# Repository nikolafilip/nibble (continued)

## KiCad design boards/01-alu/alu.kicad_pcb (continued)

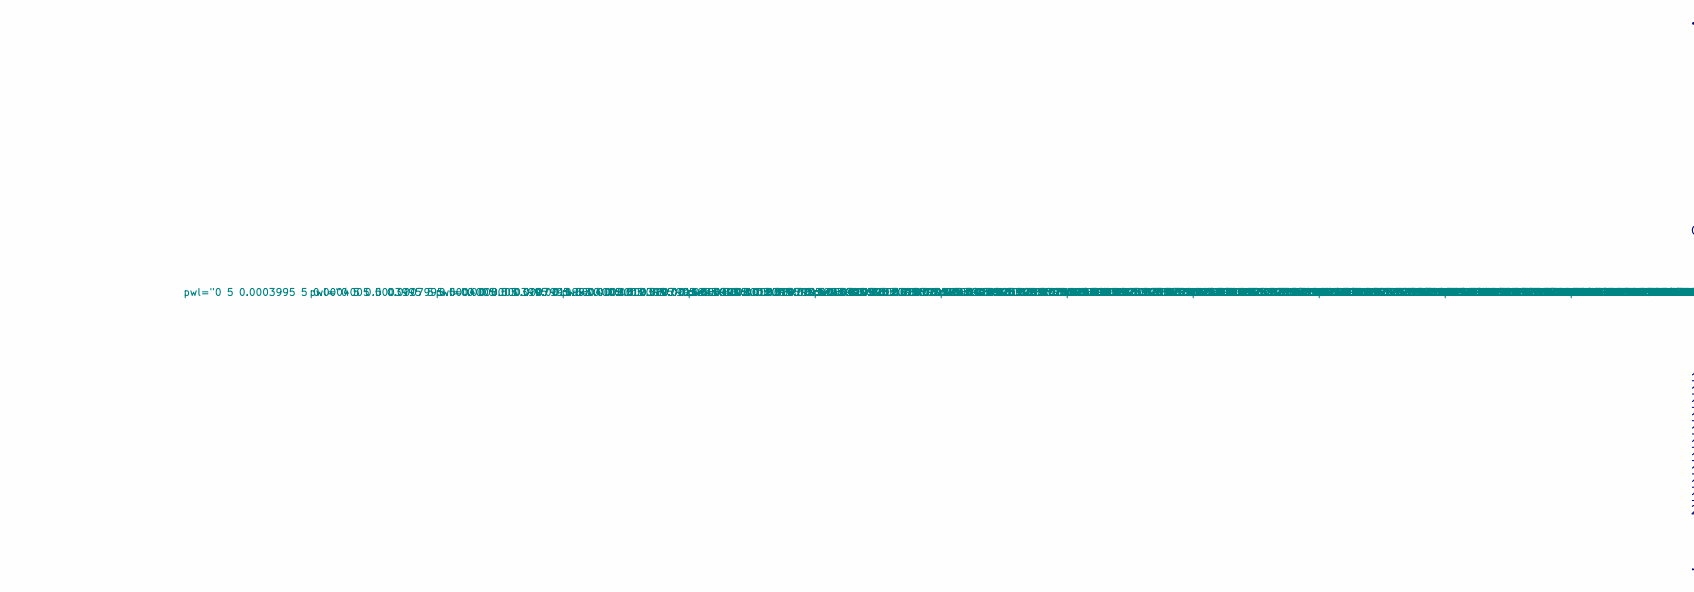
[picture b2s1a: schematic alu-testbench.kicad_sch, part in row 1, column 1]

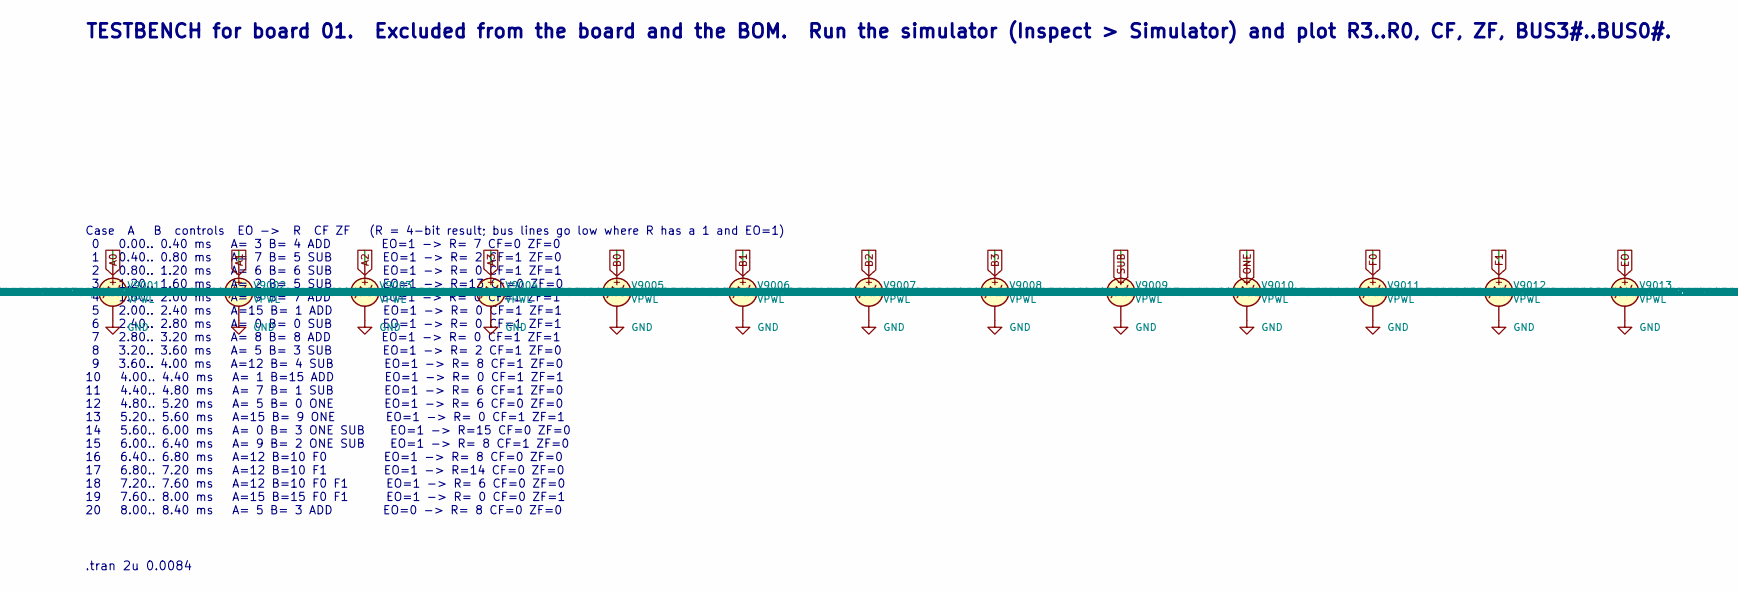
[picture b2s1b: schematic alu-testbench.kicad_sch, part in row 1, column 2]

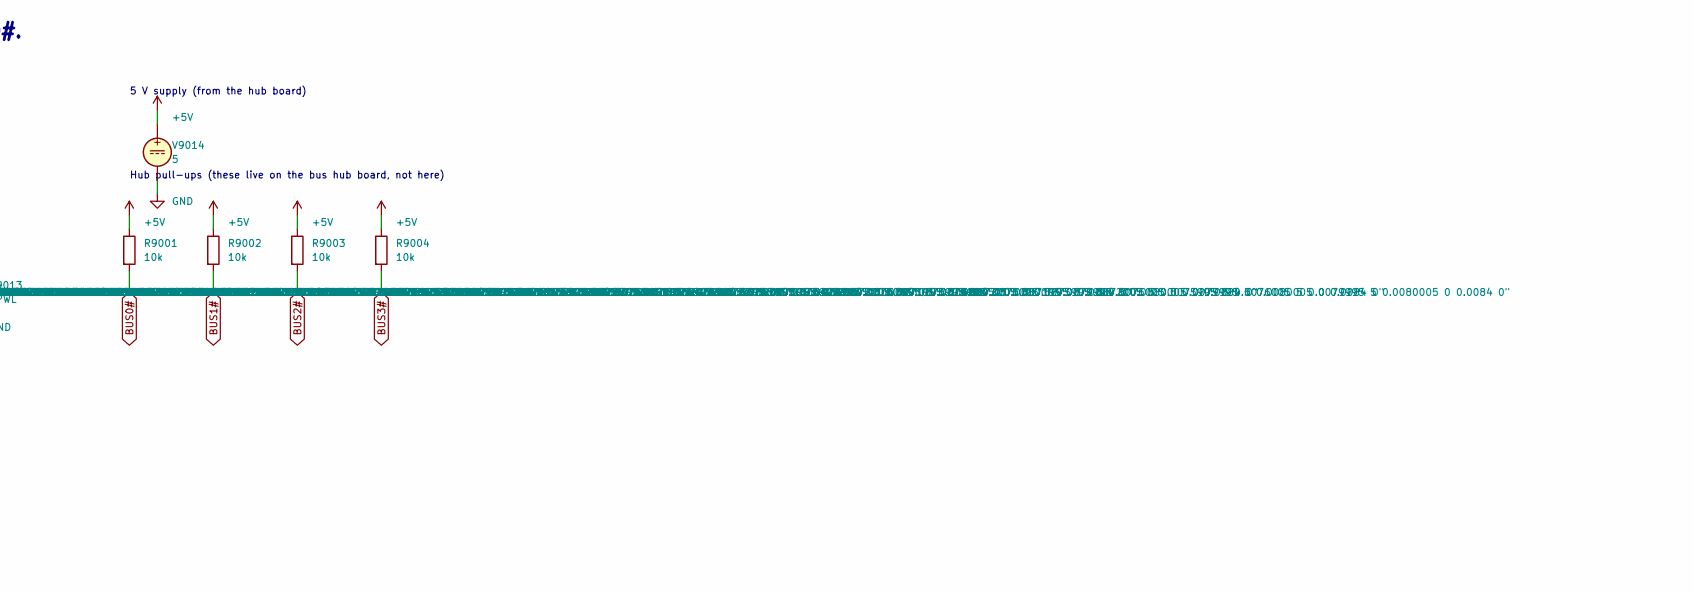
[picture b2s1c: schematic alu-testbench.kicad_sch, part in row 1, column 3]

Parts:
R9001, R9002, R9003, R9004: 10k
V9001, V9002, V9003, V9004, V9005, V9006, V9007, V9008, V9009, V9010, V9011, V9012, V9013: VPWL
V9014: 5

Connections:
unnamed: R9001.1, R9002.1, R9003.1, R9004.1, V9014.1
unnamed: V9001.2, V9002.2, V9003.2, V9004.2, V9005.2, V9006.2, V9007.2, V9008.2, V9009.2, V9010.2, V9011.2, V9012.2, V9013.2, V9014.2

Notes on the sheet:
TESTBENCH for board 01. Excluded from the board and the BOM. Run the simulator (Inspect > Simulator) and plot R3..R0, CF, ZF, BUS3#..BUS0#.
Case A B controls EO -> R CF ZF (R = 4-bit result; bus lines go low where R has a 1 and EO=1) 0 0.00.. 0.40 ms A= 3 B= 4 ADD EO=1 -> R= 7 CF=0 ZF=0 1 0.40.. 0.80 ms A= 7 B= 5 SUB EO=1 -> R= 2 CF=1 ZF=0 2 0.80.. 1.20 ms A= 6 B= 6 SUB EO=1 -> R= 0 CF=1 ZF=1 3 1.20.. 1.60 ms A= 2 B= 5 SUB EO=1 -> R=13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
.tran 2u 0.0084
5 V supply (from the hub board)
Hub pull-ups (these live on the bus hub board, not here)

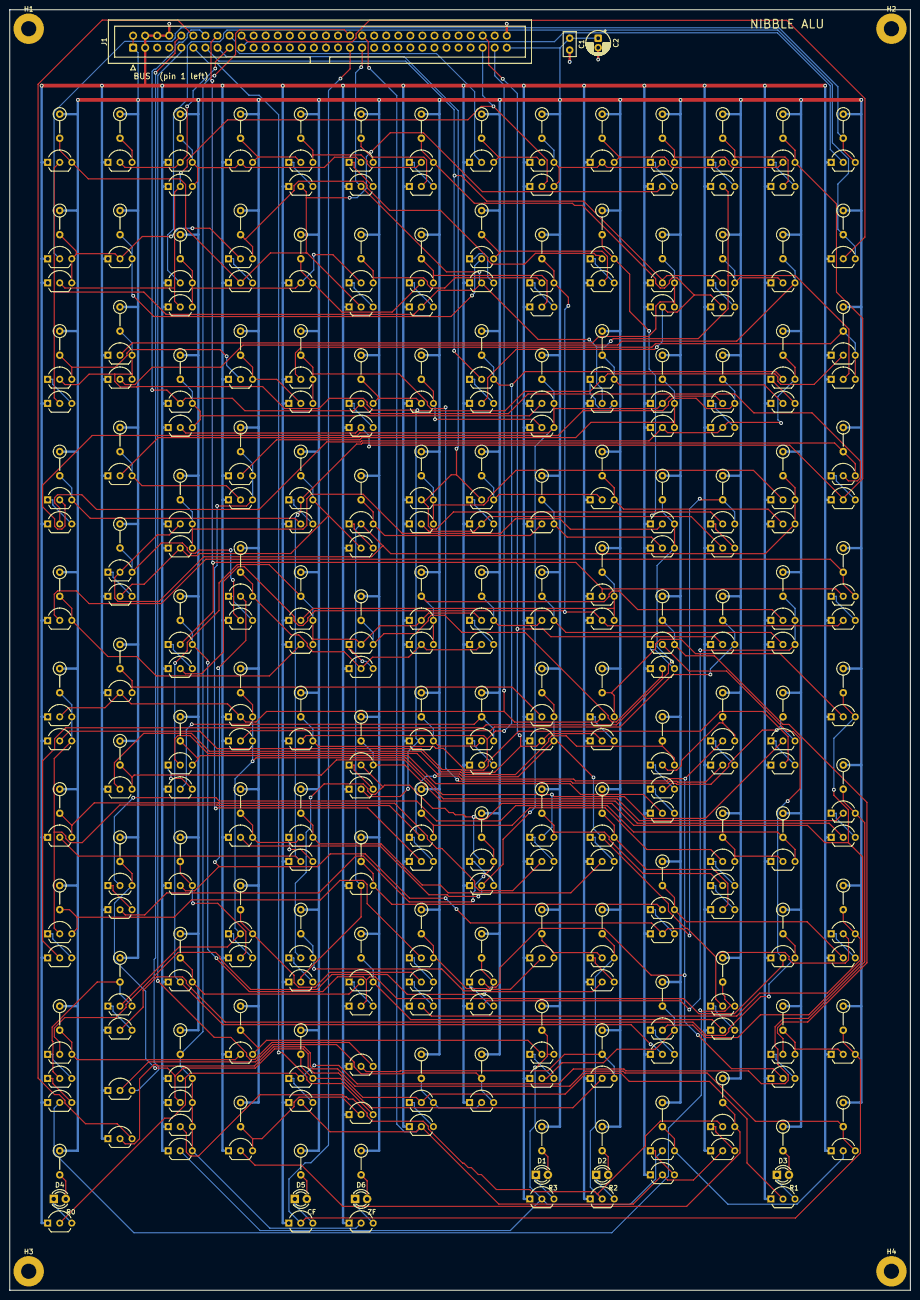
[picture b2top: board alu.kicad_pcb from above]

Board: 2 copper layers, 189.8 x 269.8 mm, 379 parts (0 on the bottom side), 228 nets.

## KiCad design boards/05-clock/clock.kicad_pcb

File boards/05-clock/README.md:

# Board 05: clock

The clock, the speed knob, the RUN/STEP switch, the halt gate and the
power-on reset. 14 transistors in cells plus the two of the Schmitt trigger,
one pot, one DIP switch, one jumper.

| | |
|---|---|
| Bus signals used | in: HLT. out: CLK, RST |

- **Oscillator**: a source-coupled Schmitt trigger (Q1 and Q2 share a 1k
  source resistor; Q2's 10k load and Q1's 47k load put the source at 0.45 V
  and 0.1 V) reads the RC node X and trips at Vth + 0.55 V going up, Vth +
  0.15 V going down. Both trip points move with the same transistor's
  threshold, so the hysteresis survives any threshold spread. Its output is
  Q2's drain, inverted by SA (4.7k pull-up), which charges X through 100k plus
  the 1M pot. 47 nF on X gives roughly 500 Hz down to 40 Hz; the SLOW jumper
  adds 2.2 uF for 10 Hz down to 0.8 Hz.
- **RUN**: the switch puts +5 V through a diode and 10k onto CLK, and the
  oscillator's transistor pulls CLK low for half of each cycle. **STEP**: the
  switch is open, the transistor is held off, and the panel's CLK button owns
  the line. The diode keeps the 10k from loading the button in STEP.
- **HLT** high holds CLK low.
- **Power-on reset**: 2.2 uF charging through 100k into a Schmitt trigger
  holds RST high for about a tenth of a second after power-up.

Three oscillators failed in simulation before this one (D036): two plain
inverters with an RC settle at a stable operating point; a MOSFET astable
falls into its both-on state; and reading the Schmitt trigger at the wrong
node let the outer loop settle half way. The mixed-threshold corner found
every one of them.

Generated by `sim/build_clock.py` from `sim/clock.py`; `sim/tb_clock.py`
measures period, duty, halt, step and the reset pulse at every corner.

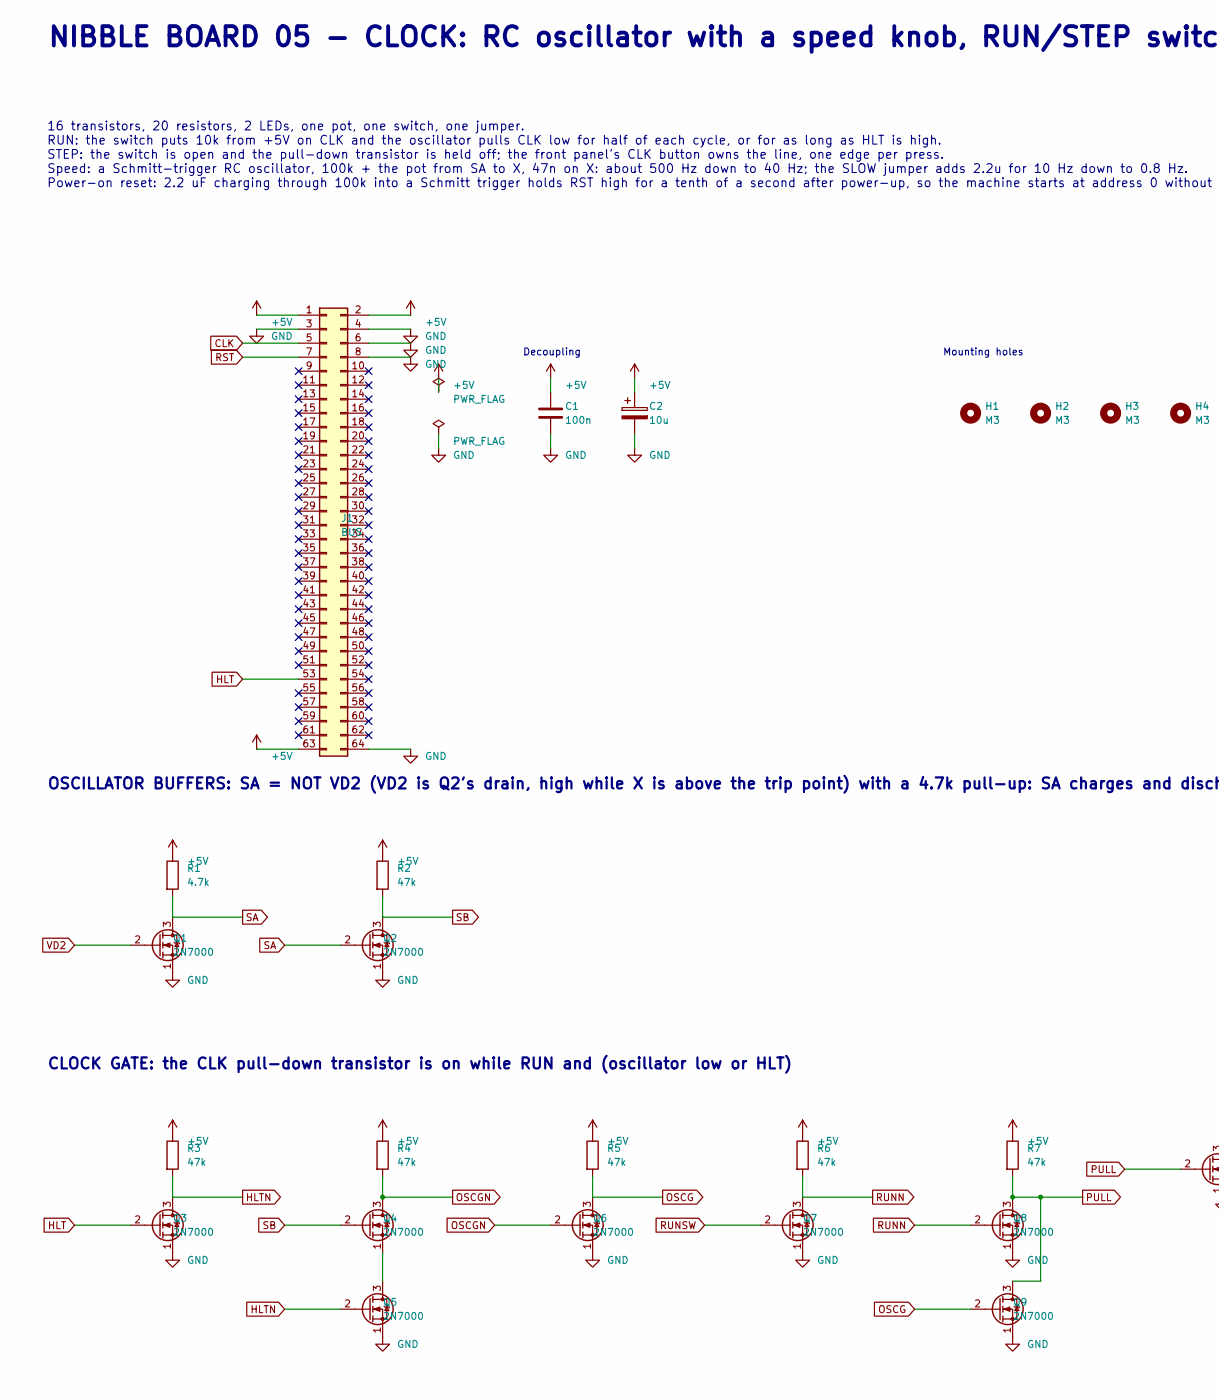
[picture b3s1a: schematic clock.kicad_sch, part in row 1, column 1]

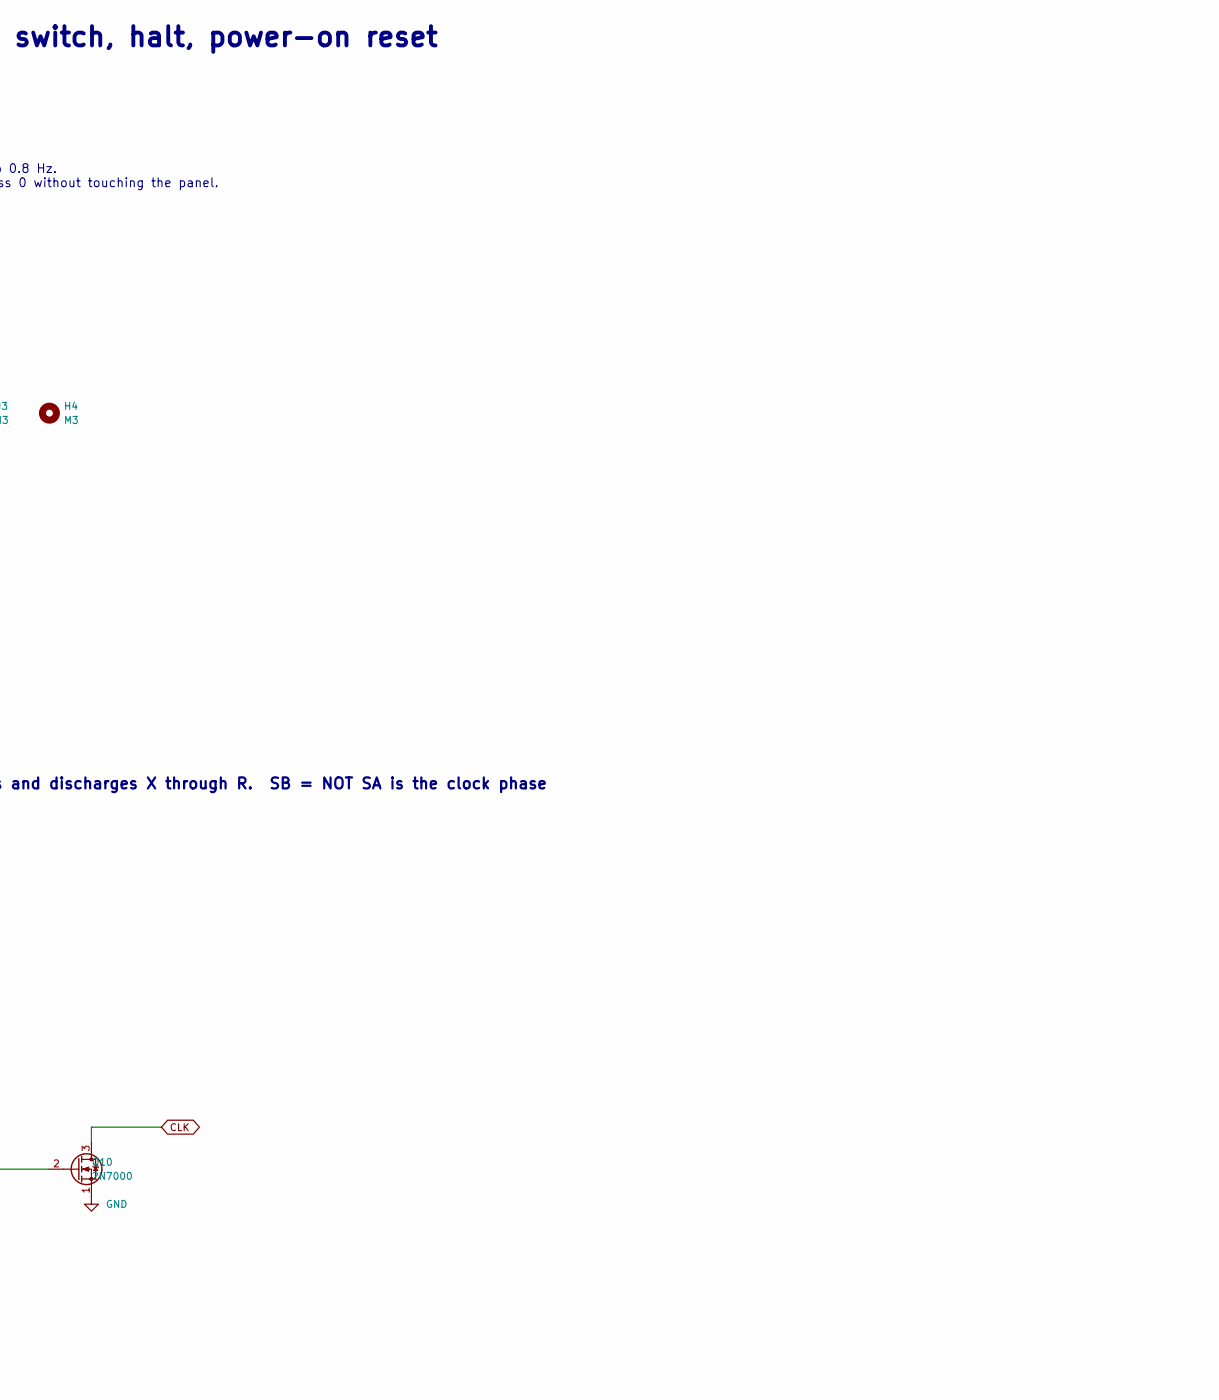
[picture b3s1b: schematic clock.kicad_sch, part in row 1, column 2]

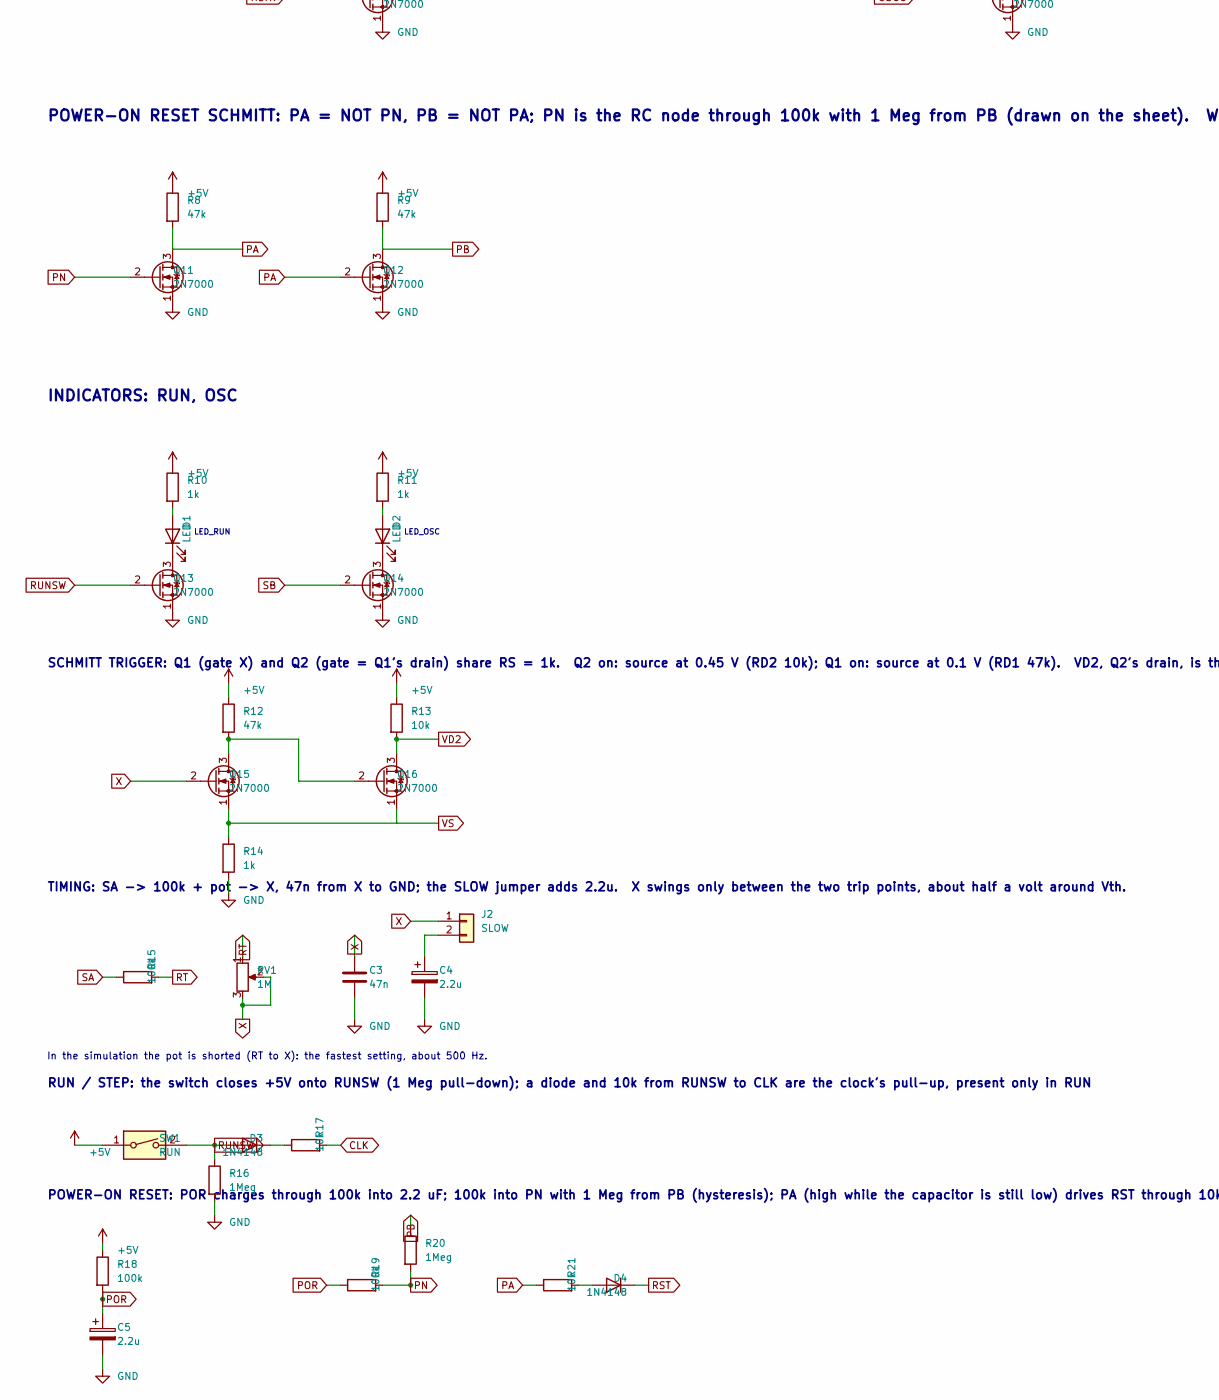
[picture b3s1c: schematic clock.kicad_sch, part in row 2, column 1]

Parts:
C1: 100n; C_Disc_D5.0mm_W2.5mm_P2.50mm
C2: 10u; CP_Radial_D5.0mm_P2.00mm
C3: 47n; C_Disc_D5.0mm_W2.5mm_P2.50mm
C4, C5: 2.2u; CP_Radial_D5.0mm_P2.00mm
D1, D2: LED; LED_D3.0mm
D3, D4: 1N4148; D_DO-35_SOD27_P7.62mm_Horizontal
H1, H2, H3, H4: M3; MountingHole_3.2mm_M3_Pad
J1: BUS; IDC-Header_2x32_P2.54mm_Vertical
J2: SLOW; PinHeader_1x02_P2.54mm_Vertical
Q1, Q2, Q3, Q4, Q5, Q6, Q7, Q8, Q9, Q10, Q11, Q12, Q13, Q14, Q15, Q16: 2N7000; TO-92_Inline_Wide
R1: 4.7k; R_Axial_DIN0207_L6.3mm_D2.5mm_P5.08mm_Vertical
R2, R3, R4, R5, R6, R7, R8, R9, R12: 47k; R_Axial_DIN0207_L6.3mm_D2.5mm_P5.08mm_Vertical
R10, R11, R14: 1k; R_Axial_DIN0207_L6.3mm_D2.5mm_P5.08mm_Vertical
R13, R17, R21: 10k; R_Axial_DIN0207_L6.3mm_D2.5mm_P5.08mm_Vertical
R15, R18, R19: 100k; R_Axial_DIN0207_L6.3mm_D2.5mm_P5.08mm_Vertical
R16, R20: 1Meg; R_Axial_DIN0207_L6.3mm_D2.5mm_P5.08mm_Vertical
RV1: 1M; Potentiometer_Alpha_RD901F-40-00D_Single_Vertical
SW1: RUN; SW_DIP_SPSTx01_Slide_9.78x4.72mm_W7.62mm_P2.54mm

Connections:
+5V: C1.1, C2.1, J1.1, J1.2, J1.63, R1.1, R2.1, R3.1, R4.1, R5.1, R6.1, R7.1, R8.1, R9.1, R10.1, R11.1, R12.1, R13.1, R18.1, SW1.1
CLK: J1.5, Q10.3 (D), R17.2
GND: C1.2, C2.2, C3.2, C4.2, C5.2, J1.3, J1.4, J1.6, J1.8, J1.64, Q1.1 (S), Q2.1 (S), Q3.1 (S), Q5.1 (S), Q6.1 (S), Q7.1 (S), Q8.1 (S), Q9.1 (S), Q10.1 (S), Q11.1 (S), Q12.1 (S), Q13.1 (S), Q14.1 (S), R14.2, R16.2
HLT: J1.53, Q3.2 (G)
HLTN: Q3.3 (D), Q5.2 (G), R3.2
unnamed: D1.2 (A), R10.2
unnamed: D1.1 (K), Q13.3 (D)
unnamed: D2.2 (A), R11.2
unnamed: D2.1 (K), Q14.3 (D)
unnamed: D3.1 (K), R17.1
unnamed: D4.2 (A), R21.2
unnamed: C4.1, J2.2
unnamed: Q4.1 (S), Q5.3 (D)
unnamed: Q15.3 (D), Q16.2 (G), R12.2
OSCG: Q6.3 (D), Q9.2 (G), R5.2
OSCGN: Q4.3 (D), Q6.2 (G), R4.2
PA: Q11.3 (D), Q12.2 (G), R8.2, R21.1
PB: Q12.3 (D), R9.2, R20.1
PN: Q11.2 (G), R19.2, R20.2
POR: C5.1, R18.2, R19.1
PULL: Q8.3 (D), Q9.3 (D), Q10.2 (G), R7.2
RST: D4.1 (K), J1.7
RT: R15.2, RV1.1
RUNN: Q7.3 (D), Q8.2 (G), R6.2
RUNSW: D3.2 (A), Q7.2 (G), Q13.2 (G), R16.1, SW1.2
SA: Q1.3 (D), Q2.2 (G), R1.2, R15.1
SB: Q2.3 (D), Q4.2 (G), Q14.2 (G), R2.2
VD2: Q1.2 (G), Q16.3 (D), R13.2
VS: Q15.1 (S), Q16.1 (S), R14.1
X: C3.1, J2.1, Q15.2 (G), RV1.2, RV1.3

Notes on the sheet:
NIBBLE BOARD 05 - CLOCK: RC oscillator with a speed knob, RUN/STEP switch, halt, power-on reset
16 transistors, 20 resistors, 2 LEDs, one pot, one switch, one jumper. RUN: the switch puts 10k from +5V on CLK and the oscillator pulls CLK low for half of each cycle, or for as long as HLT is high. STEP: the switch is open and the pull-down transistor is held off; the front panel's CLK button own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
Decoupling
Mounting holes
OSCILLATOR BUFFERS: SA = NOT VD2 (VD2 is Q2's drain, high while X is above the trip point) with a 4.7k pull-up: SA charges and discharges X through R. SB = NOT SA is the clock phase
CLOCK GATE: the CLK pull-down transistor is on while RUN and (oscillator low or HLT)
POWER-ON RESET SCHMITT: PA = NOT PN, PB = NOT PA; PN is the RC node through 100k with 1 Meg from PB (drawn on the sheet). While PA is high (the capacitor still low) RST is pulled high through 10k and a diode
INDICATORS: RUN, OSC
LED_RUN
LED_OSC
SCHMITT TRIGGER: Q1 (gate X) and Q2 (gate = Q1's drain) share RS = 1k. Q2 on: source at 0.45 V (RD2 10k); Q1 on: source at 0.1 V (RD1 47k). VD2, Q2's drain, is the output: 0.5 V with X low, 5 V with X high.
TIMING: SA -> 100k + pot -> X, 47n from X to GND; the SLOW jumper adds 2.2u. X swings only between the two trip points, about half a volt around Vth.
In the simulation the pot is shorted (RT to X): the fastest setting, about 500 Hz.
RUN / STEP: the switch closes +5V onto RUNSW (1 Meg pull-down); a diode and 10k from RUNSW to CLK are the clock's pull-up, present only in RUN
POWER-ON RESET: POR charges through 100k into 2.2 uF; 100k into PN with 1 Meg from PB (hysteresis); PA (high while the capacitor is still low) drives RST through 10k and a diode

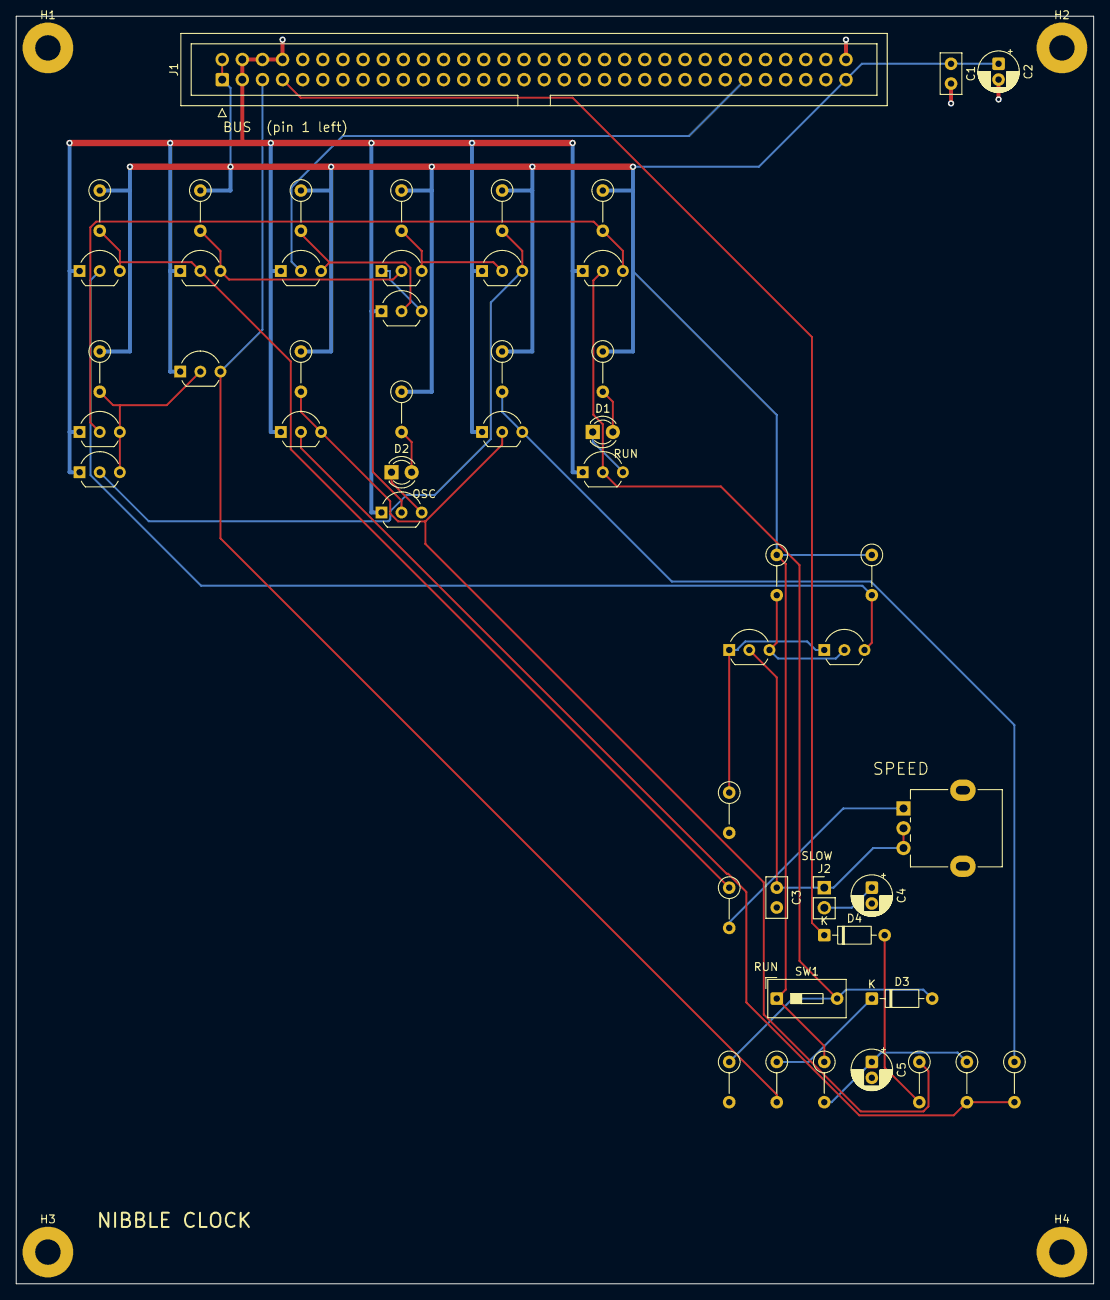
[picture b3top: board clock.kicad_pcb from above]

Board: 2 copper layers, 136.0 x 160.0 mm, 54 parts (0 on the bottom side), 30 nets.

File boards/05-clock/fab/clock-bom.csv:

"Reference","Value","Footprint","QUANTITY"
"C1","100n","Capacitor_THT:C_Disc_D5.0mm_W2.5mm_P2.50mm","1"
"C2","10u","Capacitor_THT:CP_Radial_D5.0mm_P2.00mm","1"
"C3","47n","Capacitor_THT:C_Disc_D5.0mm_W2.5mm_P2.50mm","1"
"C4,C5","2.2u","Capacitor_THT:CP_Radial_D5.0mm_P2.00mm","2"
"D1,D2","LED","LED_THT:LED_D3.0mm","2"
"D3,D4","1N4148","Diode_THT:D_DO-35_SOD27_P7.62mm_Horizontal","2"
"J1","BUS","Connector_IDC:IDC-Header_2x32_P2.54mm_Vertical","1"
"J2","SLOW","Connector_PinHeader_2.54mm:PinHeader_1x02_P2.54mm_Vertical","1"
"Q1-Q16","2N7000","Package_TO_SOT_THT:TO-92_Inline_Wide","16"
"R1","4.7k","Resistor_THT:R_Axial_DIN0207_L6.3mm_D2.5mm_P5.08mm_Vertical","1"
"R2-R9,R12","47k","Resistor_THT:R_Axial_DIN0207_L6.3mm_D2.5mm_P5.08mm_Vertical","9"
"R10,R11,R14","1k","Resistor_THT:R_Axial_DIN0207_L6.3mm_D2.5mm_P5.08mm_Vertical","3"
"R13,R17,R21","10k","Resistor_THT:R_Axial_DIN0207_L6.3mm_D2.5mm_P5.08mm_Vertical","3"
"R15,R18,R19","100k","Resistor_THT:R_Axial_DIN0207_L6.3mm_D2.5mm_P5.08mm_Vertical","3"
"R16,R20","1Meg","Resistor_THT:R_Axial_DIN0207_L6.3mm_D2.5mm_P5.08mm_Vertical","2"
"RV1","1M","Potentiometer_THT:Potentiometer_Alpha_RD901F-40-00D_Single_Vertical","1"
"SW1","RUN","Button_Switch_THT:SW_DIP_SPSTx01_Slide_9.78x4.72mm_W7.62mm_P2.54mm","1"
